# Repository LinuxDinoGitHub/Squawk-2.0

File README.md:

# Squawk-2.0
A radio station with a storage unit for walkie-talkies, w/ OLED screen & 3.5mm headphone jack connector
SI4844 powered with Arduino Nano, PAM8403 amplifier with the [pu2clr](https://pu2clr.github.io/SI4844/) library.

## About this project
The name "Squawk 2.0" originates from the popular TV show - Stranger Things (Season 5), where they had a master radio station for duplex transmission. Though this station cannot transmit any radio signals for walkie-talkies to pick up (due to legal reasons), it listens to the Citizens Band (CB) with 20 channels and a range of 2-3km. This is designed as a retro tabletop AM/FM/SW radio with the SI4844 chip, and also a handy storage device for the user. Planning to create walkie-talkies in the future that can connect to this station.
### Why did I make this?
Well, I needed a storage compartment for my walkie talkies and also wanted the container to be a bit more exciting than just a regular tin box. 

### How do you use it?
It's pretty simple, here is a layout of all the functions of the buttons you can press:

## Key features
- SW/MW/AM/FM radio broadcast with SI4844 IC
- Adjustable channel and volume with OLED screen indicator
- Storage compartment in 3D model
- Hinged door to access the compartment
- Arduino powered - open source code and customisable to your own liking
- USB-B connectivity
- 3.5mm headphone jack to listen to the radio independently without interrupting neighbours, like a Walkman
- Optimised 4-layer PCB (front, gnd_front, gnd_back, back) routing for good antenna connectivity

## [Schematic](https://github.com/LinuxDinoGitHub/Squawk-2.0/tree/main/pcb)

## [PCB](https://github.com/LinuxDinoGitHub/Squawk-2.0/tree/main/pcb)
A simple, 4-layer PCB. 96mm x 81mm PCB with 3 mounting holes for M3 screws.
### First layer (Front)

### Second layer (GND net)

### Third layer (GND net)

### Fourth layer (Back)

### 3D view
Front

Back

## [Firmware](https://github.com/LinuxDinoGitHub/Squawk-2.0/blob/main/firmware/firmware.ino)
After assembling your PCB, use the firmware.ino file in the repository to flash your Arduino Nano. You can customise messages and timings by editing the code with the Arduino IDE.

## BOM
The BOM **without** specific values is linked here ([GitHub directory](https://github.com/LinuxDinoGitHub/Squawk-2.0/blob/main/BOM_kicad_generated.csv) or [Google Sheets](https://docs.google.com/spreadsheets/d/1nt2ZC4SuuWCHXpdcqgjWmxoxNzFQoS0aQbvXVXabcSM/edit?gid=0#gid=0). The total cost for the project should not exceed 13USD (after averaging costs out by dividing by the bulk bought quantity).

The BOM **with** specific values is here (Github [directory](https://github.com/LinuxDinoGitHub/Squawk-2.0/blob/main/BOM_with_links.csv) or [Google Sheets](https://docs.google.com/spreadsheets/d/1nt2ZC4SuuWCHXpdcqgjWmxoxNzFQoS0aQbvXVXabcSM/edit?gid=1614936167#gid=1614936167))

### 3D printed case
Use a slicer to print the following [file](https://github.com/LinuxDinoGitHub/Squawk-2.0/blob/main/models/Radio.step). The 3D printed case is not accounted for in the BOM due to the variation between suppliers. The expected filament cost is around 10$ USD.

## Zine page

## Credits
Huge thanks to Ricardo for his amazing library and intuitive example code for the SI4844, which genuinely saved me so much time. [Link](https://pu2clr.github.io/SI4844/) to his repo and library. Thanks to the amazing community from Hack Club fallout for helping out my design as well, I couldn't have done it without them.

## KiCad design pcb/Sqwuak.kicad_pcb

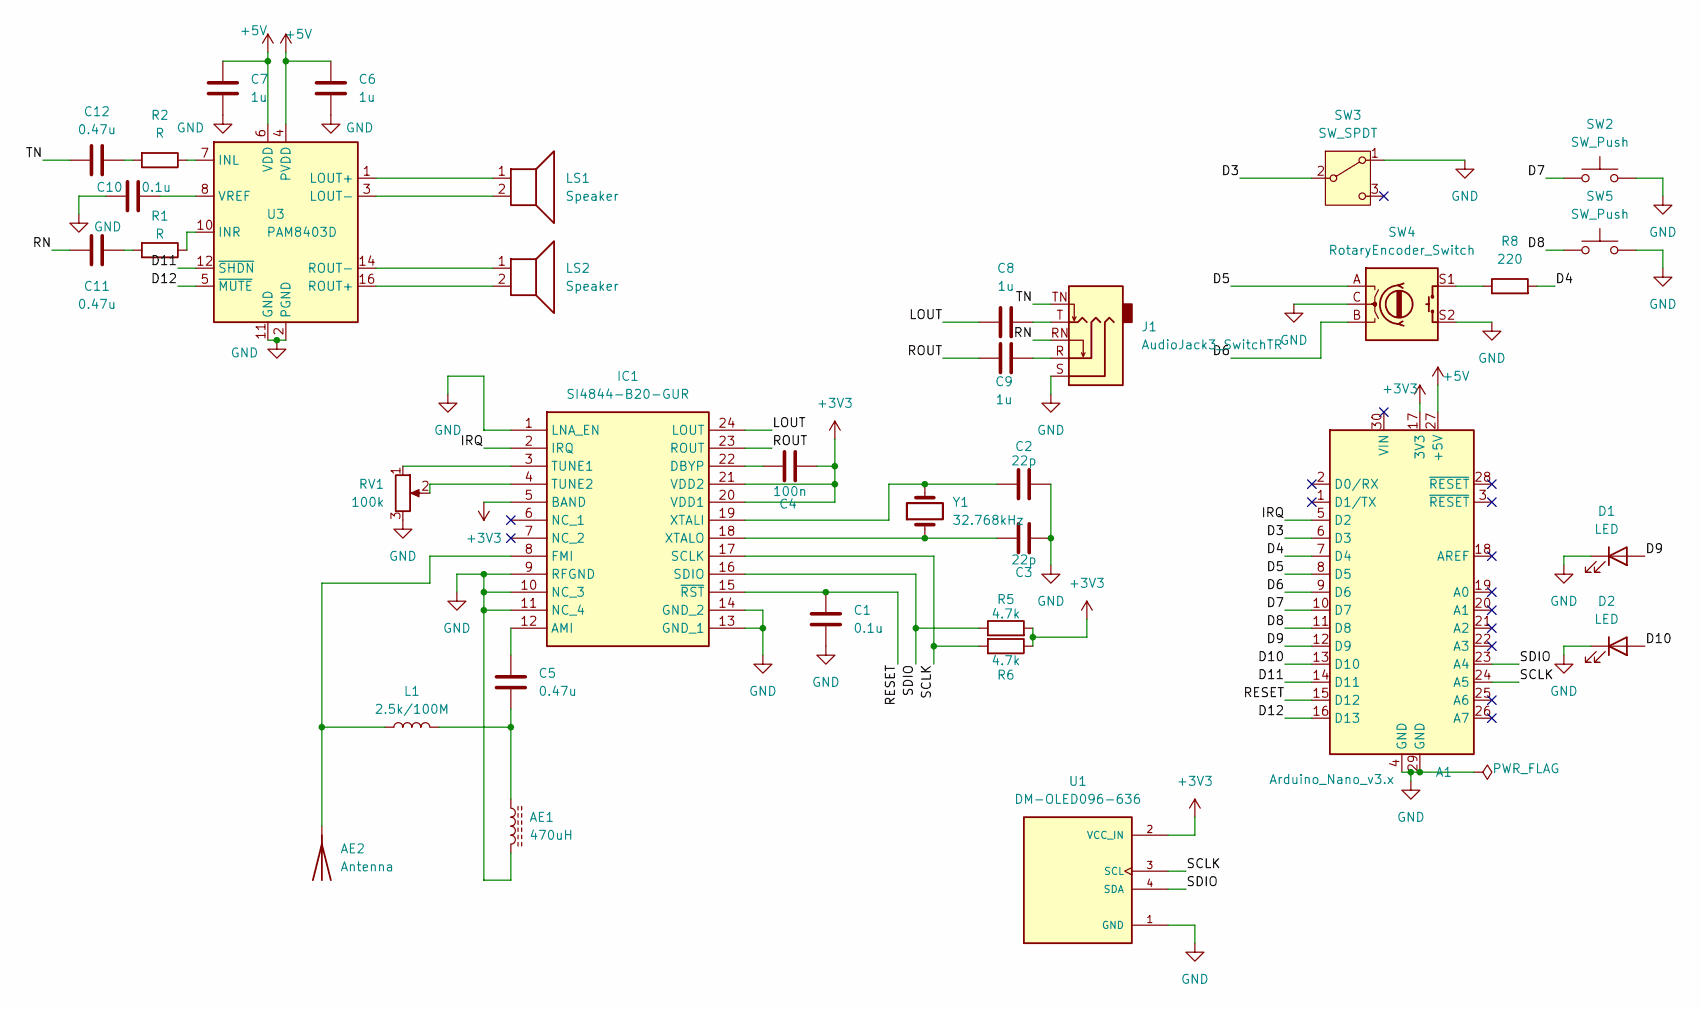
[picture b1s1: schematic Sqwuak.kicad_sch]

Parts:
A1: Arduino_Nano_v3.x; Arduino_Nano
AE1: 470uH; PinHeader_1x02_P2.54mm_Horizontal
AE2: Antenna; PinHeader_1x01_P2.54mm_Horizontal
C1, C10: 0.1u; C_Disc_D3.8mm_W2.6mm_P2.50mm
C2, C3: 22p; C_Disc_D3.8mm_W2.6mm_P2.50mm
C4: 100n; C_Disc_D3.8mm_W2.6mm_P2.50mm
C5, C11, C12: 0.47u; C_Disc_D3.8mm_W2.6mm_P2.50mm
C6, C7, C8, C9: 1u; C_Disc_D3.8mm_W2.6mm_P2.50mm
D1, D2: LED; LED_D1.8mm_W1.8mm_H2.4mm_Horizontal_O1.27mm_Z1.6mm
IC1: SI4844-B20-GUR; SOP64P600X175-24N; Manufacturer_Part_Number SI4844-B20-GUR; Mouser Part Number 634-SI4844-B20-GUR
J1: AudioJack3_SwitchTR; Jack_3.5mm_CUI_SJ1-3525N_Horizontal
L1: 2.5k/100M; L_Axial_L7.0mm_D3.3mm_P10.16mm_Horizontal_Fastron_MICC
LS1, LS2: Speaker; PinHeader_1x02_P2.54mm_Vertical
R1, R2: R; R_Axial_DIN0207_L6.3mm_D2.5mm_P7.62mm_Horizontal
R5, R6: 4.7k; R_Axial_DIN0207_L6.3mm_D2.5mm_P7.62mm_Horizontal
R8: 220; R_Axial_DIN0207_L6.3mm_D2.5mm_P7.62mm_Horizontal
RV1: 100k; Potentiometer_Bourns_PTV09A-1_Single_Vertical
SW2, SW5: SW_Push; SW_PUSH_6mm
SW3: SW_SPDT; PinHeader_1x03_P2.54mm_Horizontal
SW4: RotaryEncoder_Switch; RotaryEncoder_Alps_EC11E-Switch_Vertical_H20mm
U1: DM-OLED096-636; MODULE_DM-OLED096-636; PARTREV 2018-09-10
U3: PAM8403D; SOIC-16_3.9x9.9mm_P1.27mm
Y1: 32.768kHz; Crystal_SMD_3215-2Pin_3.2x1.5mm

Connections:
+3V3: A1.17 (3V3), C4.2, IC1.5 (BAND), IC1.20 (VDD1), IC1.21 (VDD2), R5.2, R6.1, U1.2 (VCC_IN)
+5V: A1.27 (+5V), C6.1, C7.1, U3.4 (PVDD), U3.6 (VDD), U3.13 (PVDD)
/D3: A1.6 (D3), SW3.2 (B)
/D4: A1.7 (D4), R8.2
/D5: A1.8 (D5), SW4.A
/D6: A1.9 (D6), SW4.B
/D7: A1.10 (D7), SW2.1
/D8: A1.11 (D8), SW5.1
/D9: A1.12 (D9), D1.2 (A)
/D10: A1.13 (D10), D2.2 (A)
/D11: A1.14 (D11), U3.12 (~SHDN)
/D12: A1.16 (D13), U3.5 (~MUTE)
/IRQ: A1.5 (D2), IC1.2 (IRQ)
/LOUT: C8.1, IC1.24 (LOUT)
/RESET: A1.15 (D12), C1.1, IC1.15 (~RST)
/RN: C11.2, J1.RN
/ROUT: C9.2, IC1.23 (ROUT)
/SCLK: A1.24 (A5), IC1.17 (SCLK), R6.2, U1.3 (SCL)
/SDIO: A1.23 (A4), IC1.16 (SDIO), R5.1, U1.4 (SDA)
/TN: C12.2, J1.TN
GND: A1.4 (GND), A1.29 (GND), AE1.2, C1.2, C2.2, C3.1, C6.2, C7.2, C10.2, D1.1 (K), D2.1 (K), IC1.1 (LNA_EN), IC1.9 (RFGND), IC1.10 (NC_3), IC1.11 (NC_4), IC1.13 (GND_1), IC1.14 (GND_2), J1.S, RV1.3, SW2.2, SW3.1 (A), SW4.C, SW4.S2, SW5.2, U1.1 (GND), U3.2 (PGND), U3.11 (GND), U3.15 (PGND)
unnamed: AE1.1, C5.2, L1.2
unnamed: AE2.1 (A_1), IC1.8 (FMI), L1.1
unnamed: C8.2, J1.T
unnamed: C9.1, J1.R
unnamed: C11.1, R1.2
unnamed: C12.1, R2.2
unnamed: C5.1, IC1.12 (AMI)
unnamed: C4.1, IC1.22 (DBYP)
unnamed: IC1.3 (TUNE1), RV1.1
unnamed: IC1.4 (TUNE2), RV1.2
unnamed: C2.1, IC1.19 (XTALI), Y1.2
unnamed: C3.2, IC1.18 (XTALO), Y1.1
unnamed: R8.1, SW4.S1
unnamed: R2.1, U3.7 (INL)
unnamed: R1.1, U3.10 (INR)
unnamed: LS1.1, U3.1 (LOUT+)
unnamed: LS1.2, U3.3 (LOUT-)
unnamed: LS2.2, U3.16 (ROUT+)
unnamed: LS2.1, U3.14 (ROUT-)
unnamed: C10.1, U3.8 (VREF)

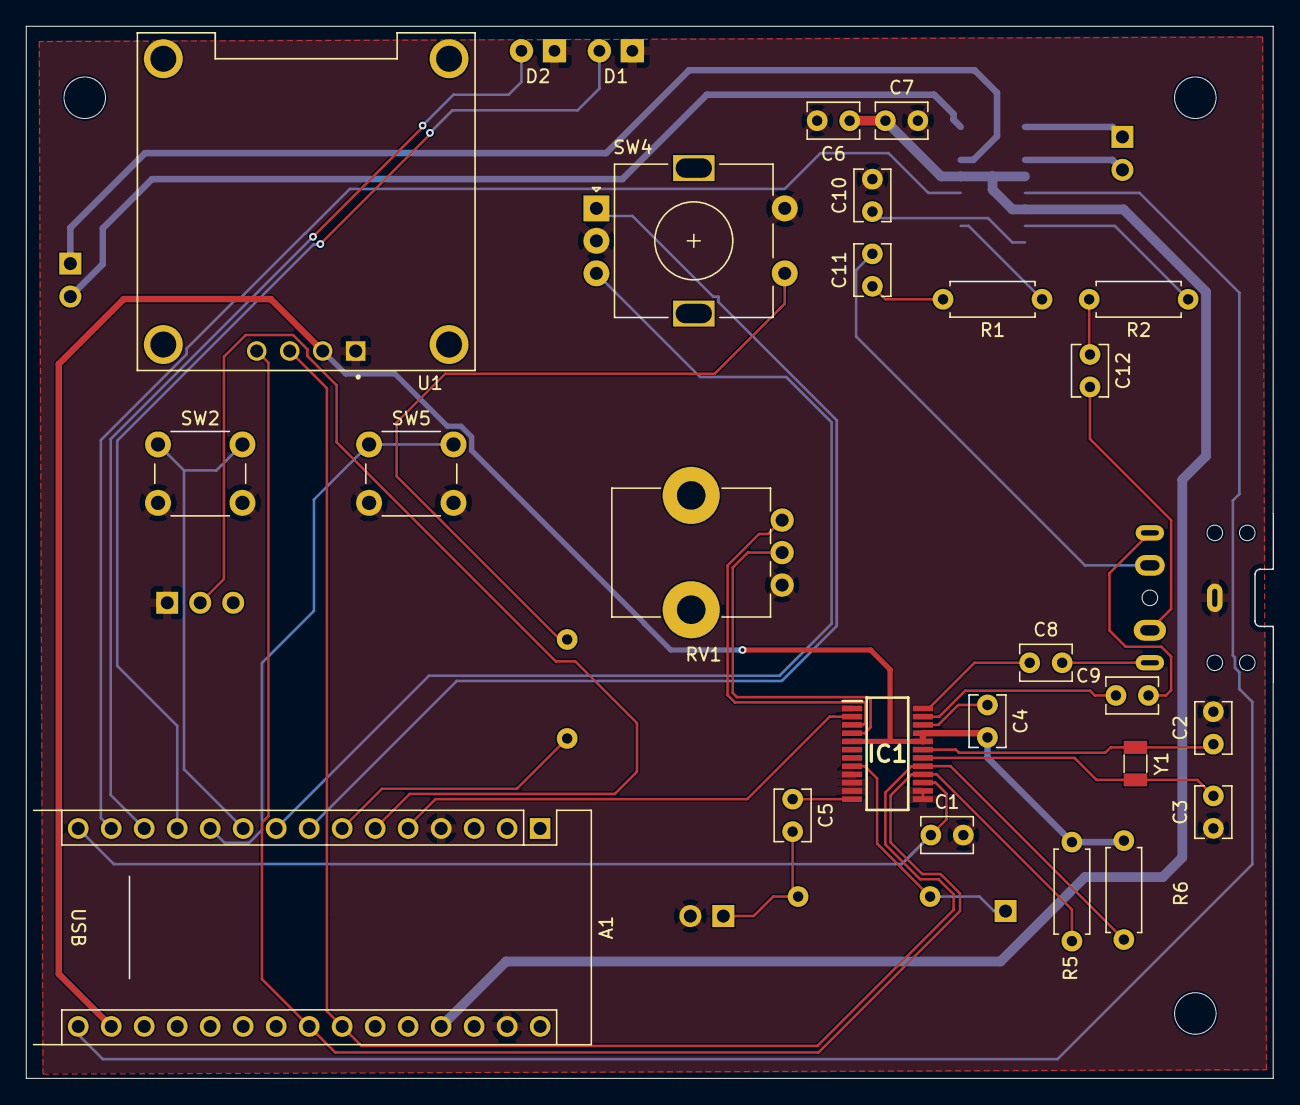
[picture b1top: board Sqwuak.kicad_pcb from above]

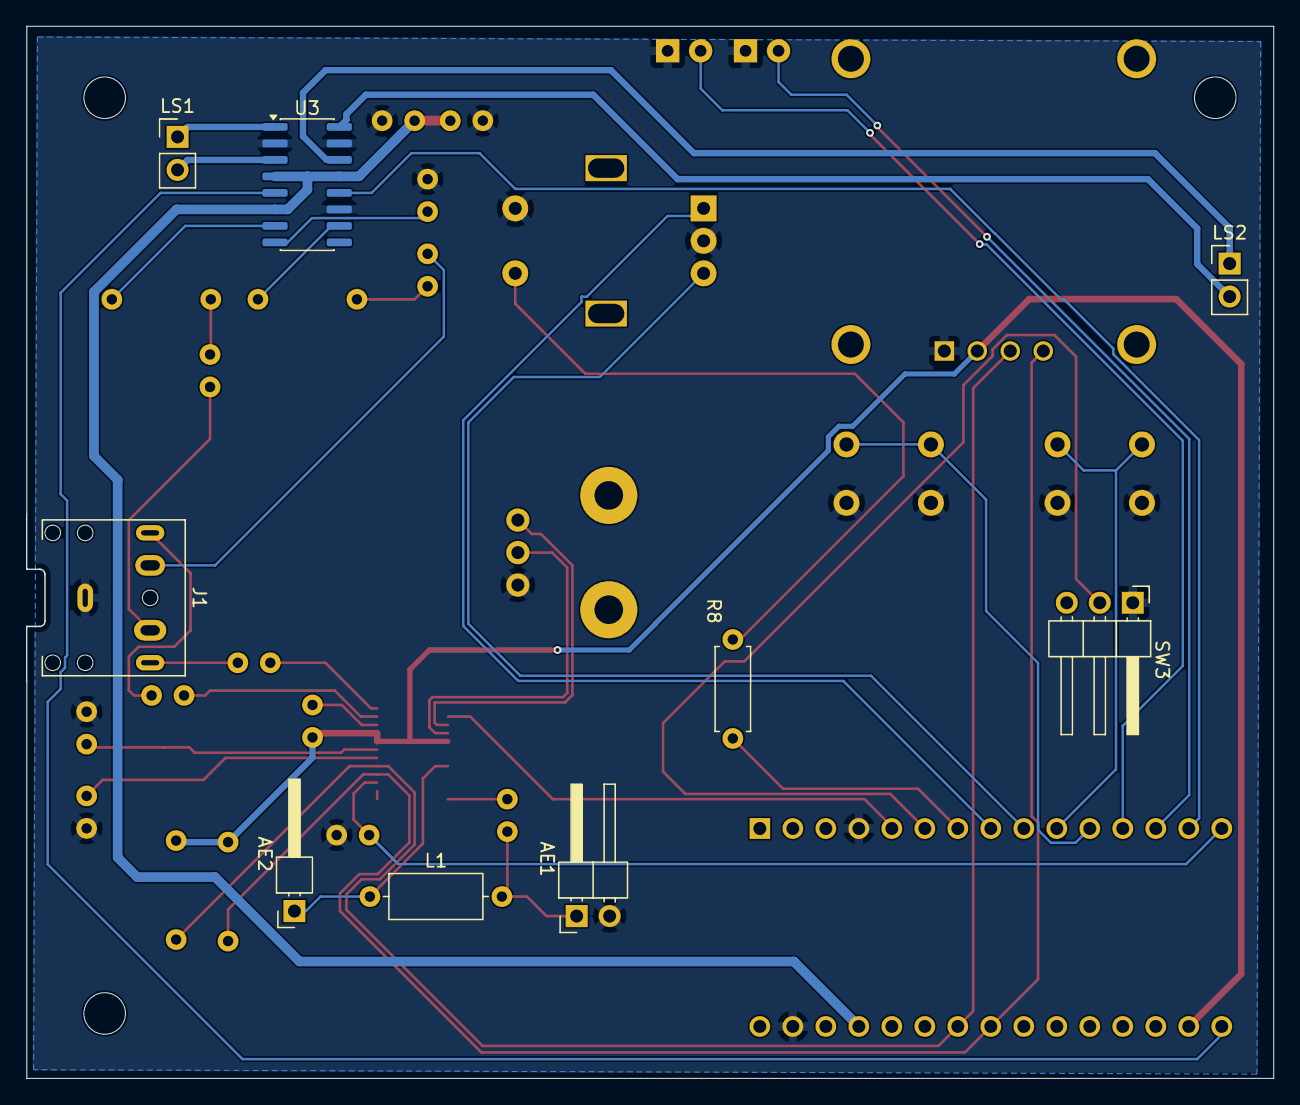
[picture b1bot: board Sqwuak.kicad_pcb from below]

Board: 2 copper layers, 96.0 x 80.9 mm, 35 parts (9 on the bottom side), 41 nets.

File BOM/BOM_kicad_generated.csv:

"Reference","Qty","Value","DNP","Exclude from BOM","Exclude from Board","Footprint","Datasheet"
"A1","1","Arduino_Nano_v3.x","","","","Module:Arduino_Nano","http://www.mouser.com/pdfdocs/Gravitech_Arduino_Nano3_0.pdf"
"AE1","1","470uH","","","","Connector_PinHeader_2.54mm:PinHeader_1x02_P2.54mm_Horizontal",""
"AE2","1","Antenna","","","","Connector_PinHeader_2.54mm:PinHeader_1x01_P2.54mm_Horizontal",""
"C1,C10","2","0.1u","","","","Capacitor_THT:C_Disc_D3.8mm_W2.6mm_P2.50mm",""
"C2,C3","2","22p","","","","Capacitor_THT:C_Disc_D3.8mm_W2.6mm_P2.50mm",""
"C4","1","100n","","","","Capacitor_THT:C_Disc_D3.8mm_W2.6mm_P2.50mm",""
"C5,C11,C12","3","0.47u","","","","Capacitor_THT:C_Disc_D3.8mm_W2.6mm_P2.50mm",""
"C6,C7,C8,C9","4","1u","","","","Capacitor_THT:C_Disc_D3.8mm_W2.6mm_P2.50mm",""
"D1,D2","2","LED","","","","LED_THT:LED_D1.8mm_W1.8mm_H2.4mm_Horizontal_O1.27mm_Z1.6mm",""
"IC1","1","SI4844-B20-GUR","","","","KiCad2:SOP64P600X175-24N","https://www.mouser.com/datasheet/2/472/Si4844_B20-2507496.pdf"
"J1","1","AudioJack3_SwitchTR","","","","Connector_Audio:Jack_3.5mm_CUI_SJ1-3525N_Horizontal",""
"L1","1","2.5k/100M","","","","Inductor_THT:L_Axial_L7.0mm_D3.3mm_P10.16mm_Horizontal_Fastron_MICC",""
"LS1,LS2","2","Speaker","","","","Connector_PinHeader_2.54mm:PinHeader_1x02_P2.54mm_Vertical",""
"R1,R2","2","R","","","","Resistor_THT:R_Axial_DIN0207_L6.3mm_D2.5mm_P7.62mm_Horizontal",""
"R5,R6","2","4.7k","","","","Resistor_THT:R_Axial_DIN0207_L6.3mm_D2.5mm_P7.62mm_Horizontal",""
"R8","1","220","","","","Resistor_THT:R_Axial_DIN0207_L6.3mm_D2.5mm_P7.62mm_Horizontal",""
"RV1","1","100k","","","","Potentiometer_THT:Potentiometer_Bourns_PTV09A-1_Single_Vertical",""
"SW2,SW5","2","SW_Push","","","","Button_Switch_THT:SW_PUSH_6mm",""
"SW3","1","SW_SPDT","","","","Connector_PinHeader_2.54mm:PinHeader_1x03_P2.54mm_Horizontal",""
"SW4","1","RotaryEncoder_Switch","","","","Rotary_Encoder:RotaryEncoder_Alps_EC11E-Switch_Vertical_H20mm",""
"U1","1","DM-OLED096-636","","","","DM-OLED096-636:MODULE_DM-OLED096-636",""
"U3","1","PAM8403D","","","","Package_SO:SOIC-16_3.9x9.9mm_P1.27mm","https://www.diodes.com/assets/Datasheets/products_inactive_d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"
"Y1","1","32.768kHz","","","","Crystal:Crystal_SMD_3215-2Pin_3.2x1.5mm",""

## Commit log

2026-04-14 Update README with project details and schematic
    Expanded project description and added schematic and BOM sections.
2026-04-15 Added schematic files just to backup
2026-04-27 Finished all files
2026-04-27 Update README with project details and features
    Expanded project description and added key features, schematic, PCB details, firmware instructions, and BOM links.
2026-04-27 Fixed links
2026-04-27 Added 3D models and BOM
2026-04-29 Finished Zine pages and added 3D models
2026-04-29 Removed big files
2026-04-29 Added Zine png
2026-04-29 Added links in README
2026-04-29 Added instructions
2026-04-29 Added credit for ricardo
2026-04-29 renamed a whole lotta file names
2026-04-29 Removed an image from README
2026-04-30 added step files for individual 3D printing
2026-04-30 Replace schematic image with updated version
    Updated schematic image in README with new dimensions.
2026-04-30 Revise BOM section in README
    Updated BOM section with links to specific and non-specific values.
2026-04-30 added assets for the schematic
2026-05-09 zipped gerbers
